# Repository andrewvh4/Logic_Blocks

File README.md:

# Logic_Blocks
Modular, schematic-friendly logic blocks perfect for elementary experimentation with Digital Logic

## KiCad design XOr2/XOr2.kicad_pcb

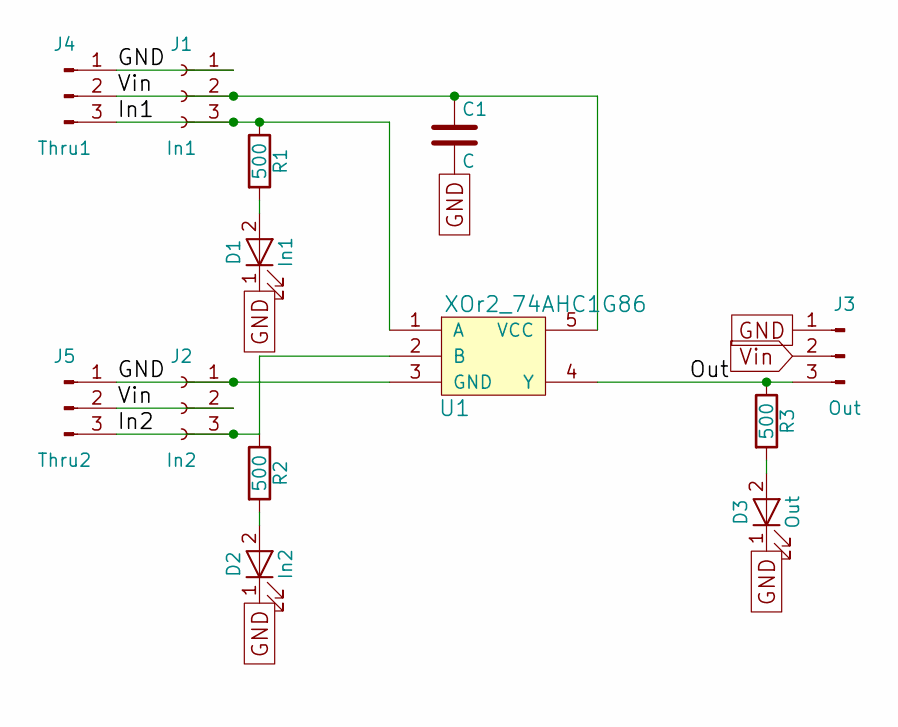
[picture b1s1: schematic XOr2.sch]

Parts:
C1: C; C_0603_HandSoldering
D1: In1; LED_0603_HandSoldering
D2: In2; LED_0603_HandSoldering
D3: Out; LED_0603_HandSoldering
J1: In1; Socket_Strip_Angled_1x03_Pitch2.54mm
J2: In2; Socket_Strip_Angled_1x03_Pitch2.54mm
J3: Out; Pin_Header_Angled_1x03_Pitch2.54mm
J4: Thru1; Pin_Header_Angled_1x03_Pitch2.54mm
J5: Thru2; Pin_Header_Angled_1x03_Pitch2.54mm
R1, R2, R3: 500; R_0603_HandSoldering
U1: XOr2_74AHC1G86; SC_70_1.25mm

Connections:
/In1: J1.3, J4.3, R1.1, U1.1 (A)
/In2: J2.3, J5.3, R2.1, U1.2 (B)
/Out: J3.3, R3.1, U1.4 (Y)
GND: C1.2, D1.1 (K), D2.1 (K), D3.1 (K), J1.1, J2.1, J3.1, J4.1, J5.1, U1.3 (GND)
unnamed: D1.2 (A), R1.2
unnamed: D2.2 (A), R2.2
unnamed: D3.2 (A), R3.2
Vin: C1.1, J1.2, J2.2, J3.2, J4.2, J5.2, U1.5 (VCC)

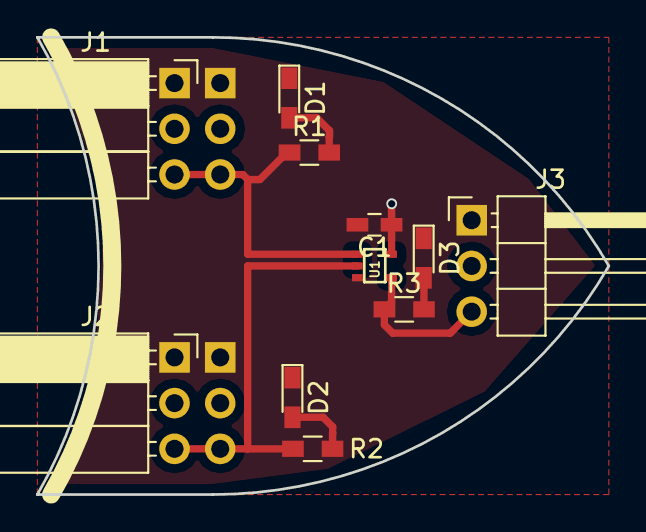
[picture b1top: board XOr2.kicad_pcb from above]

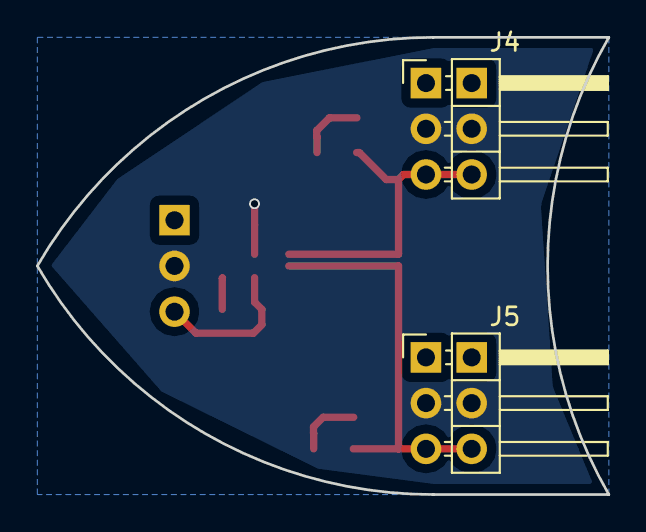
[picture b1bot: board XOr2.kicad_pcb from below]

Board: 2 copper layers, 31.7 x 25.4 mm, 13 parts (2 on the bottom side), 8 nets.

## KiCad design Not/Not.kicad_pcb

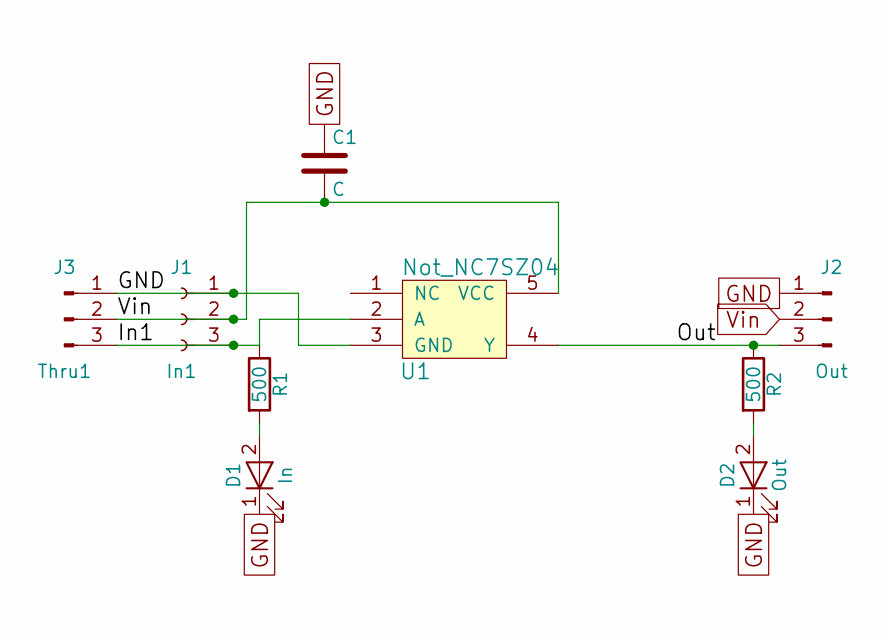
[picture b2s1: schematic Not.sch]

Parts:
C1: C; C_0603_HandSoldering
D1: In; LED_0603_HandSoldering
D2: Out; LED_0603_HandSoldering
J1: In1; Socket_Strip_Angled_1x03_Pitch2.54mm
J2: Out; Pin_Header_Angled_1x03_Pitch2.54mm
J3: Thru1; Pin_Header_Angled_1x03_Pitch2.54mm
R1, R2: 500; R_0603_HandSoldering
U1: Not_NC7SZ04; SC_70_1.25mm

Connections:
/In1: J1.3, J3.3, R1.1, U1.2 (A)
/Out: J2.3, R2.1, U1.4 (Y)
GND: C1.1, D1.1 (K), D2.1 (K), J1.1, J2.1, J3.1, U1.3 (GND)
unnamed: D1.2 (A), R1.2
unnamed: D2.2 (A), R2.2
Vin: C1.2, J1.2, J2.2, J3.2, U1.5 (VCC)

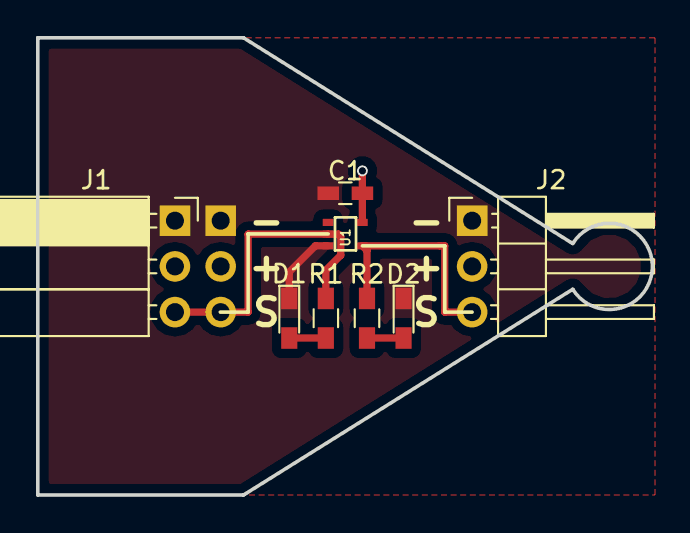
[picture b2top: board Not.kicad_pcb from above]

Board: 2 copper layers, 34.1 x 25.4 mm, 9 parts (1 on the bottom side), 6 nets.

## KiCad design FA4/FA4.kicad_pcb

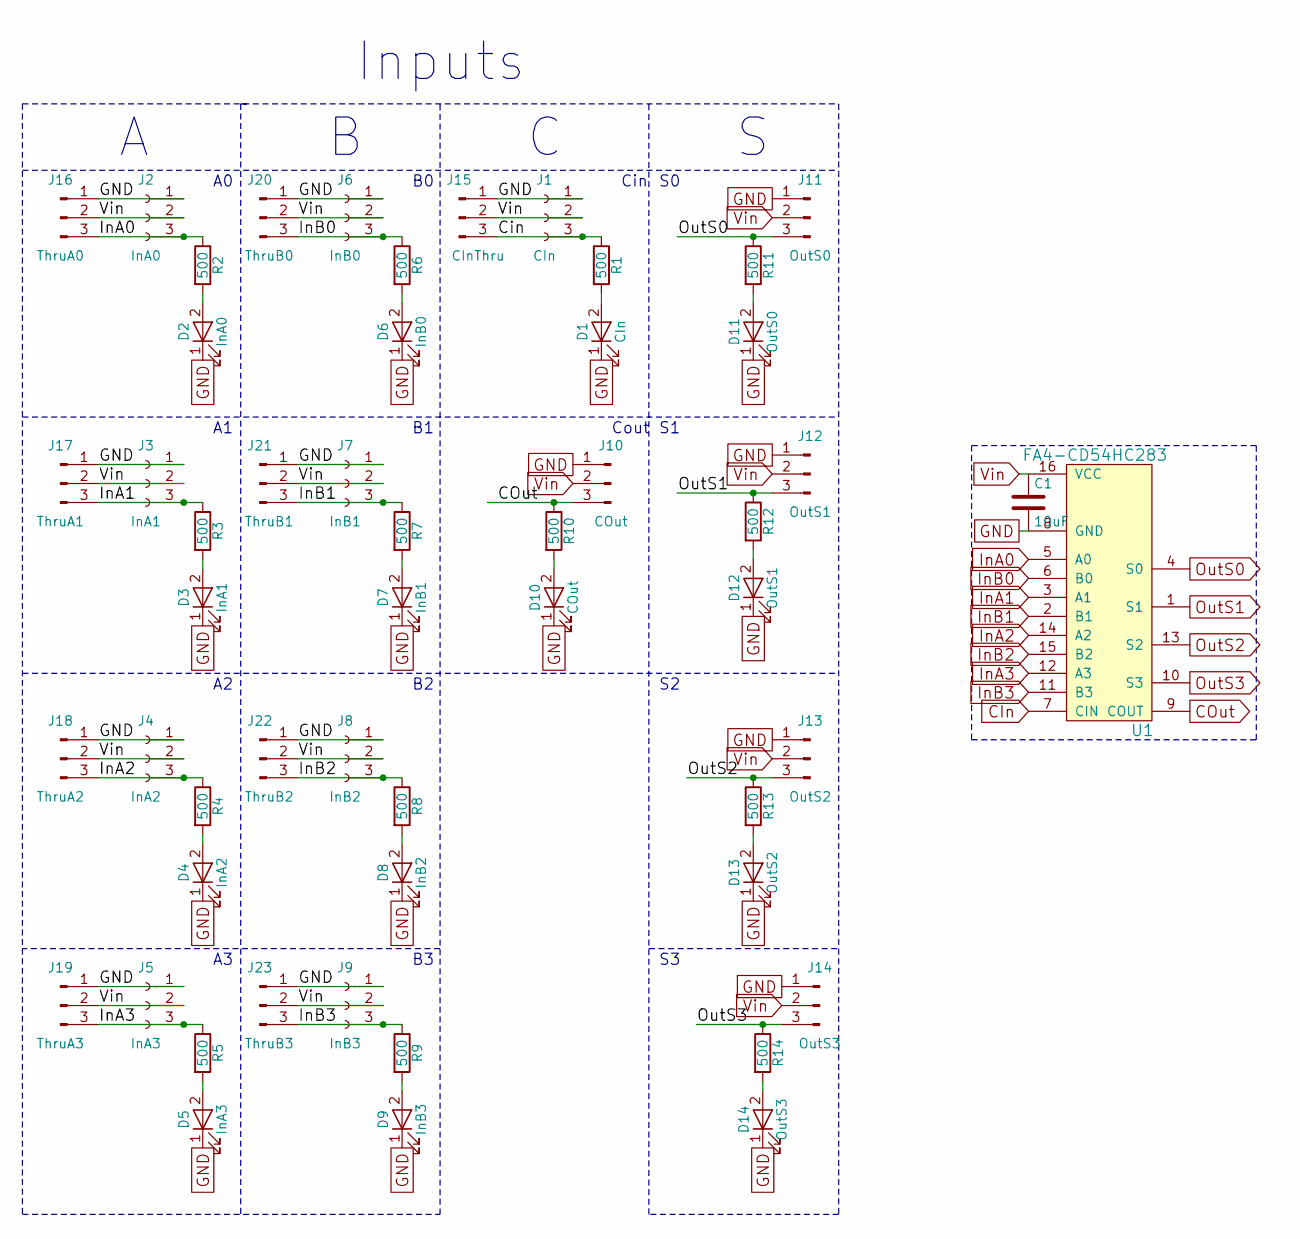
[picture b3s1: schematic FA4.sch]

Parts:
C1: 10uF; C_0603_HandSoldering
D1: CIn; LED_0603_HandSoldering
D2: InA0; LED_0603_HandSoldering
D3: InA1; LED_0603_HandSoldering
D4: InA2; LED_0603_HandSoldering
D5: InA3; LED_0603_HandSoldering
D6: InB0; LED_0603_HandSoldering
D7: InB1; LED_0603_HandSoldering
D8: InB2; LED_0603_HandSoldering
D9: InB3; LED_0603_HandSoldering
D10: COut; LED_0603_HandSoldering
D11: OutS0; LED_0603_HandSoldering
D12: OutS1; LED_0603_HandSoldering
D13: OutS2; LED_0603_HandSoldering
D14: OutS3; LED_0603_HandSoldering
J1: CIn; Socket_Strip_Angled_1x03_Pitch2.54mm
J2: InA0; Socket_Strip_Angled_1x03_Pitch2.54mm
J3: InA1; Socket_Strip_Angled_1x03_Pitch2.54mm
J4: InA2; Socket_Strip_Angled_1x03_Pitch2.54mm
J5: InA3; Socket_Strip_Angled_1x03_Pitch2.54mm
J6: InB0; Socket_Strip_Angled_1x03_Pitch2.54mm
J7: InB1; Socket_Strip_Angled_1x03_Pitch2.54mm
J8: InB2; Socket_Strip_Angled_1x03_Pitch2.54mm
J9: InB3; Socket_Strip_Angled_1x03_Pitch2.54mm
J10: COut; Pin_Header_Angled_1x03_Pitch2.54mm
J11: OutS0; Pin_Header_Angled_1x03_Pitch2.54mm
J12: OutS1; Pin_Header_Angled_1x03_Pitch2.54mm
J13: OutS2; Pin_Header_Angled_1x03_Pitch2.54mm
J14: OutS3; Pin_Header_Angled_1x03_Pitch2.54mm
J15: CInThru; Pin_Header_Angled_1x03_Pitch2.54mm
J16: ThruA0; Pin_Header_Angled_1x03_Pitch2.54mm
J17: ThruA1; Pin_Header_Angled_1x03_Pitch2.54mm
J18: ThruA2; Pin_Header_Angled_1x03_Pitch2.54mm
J19: ThruA3; Pin_Header_Angled_1x03_Pitch2.54mm
J20: ThruB0; Pin_Header_Angled_1x03_Pitch2.54mm
J21: ThruB1; Pin_Header_Angled_1x03_Pitch2.54mm
J22: ThruB2; Pin_Header_Angled_1x03_Pitch2.54mm
J23: ThruB3; Pin_Header_Angled_1x03_Pitch2.54mm
R1, R2, R3, R4, R5, R6, R7, R8, R9, R10, R11, R12, R13, R14: 500; R_0603_HandSoldering
U1: FA4-CD54HC283; SOIC-16W_5.3x10.2mm_Pitch1.27mm

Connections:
CIn: J1.3, J15.3, R1.1, U1.7 (CIN)
COut: J10.3, R10.1, U1.9 (COUT)
GND: C1.2, D1.1 (K), D2.1 (K), D3.1 (K), D4.1 (K), D5.1 (K), D6.1 (K), D7.1 (K), D8.1 (K), D9.1 (K), D10.1 (K), D11.1 (K), D12.1 (K), D13.1 (K), D14.1 (K), J1.1, J2.1, J3.1, J4.1, J5.1, J6.1, J7.1, J8.1, J9.1, J10.1, J11.1, J12.1, J13.1, J14.1, J15.1, J16.1, J17.1, J18.1, J19.1, J20.1, J21.1, J22.1, J23.1, U1.8 (GND)
InA0: J2.3, J16.3, R2.1, U1.5 (A0)
InA1: J3.3, J17.3, R3.1, U1.3 (A1)
InA2: J4.3, J18.3, R4.1, U1.14 (A2)
InA3: J5.3, J19.3, R5.1, U1.12 (A3)
InB0: J6.3, J20.3, R6.1, U1.6 (B0)
InB1: J7.3, J21.3, R7.1, U1.2 (B1)
InB2: J8.3, J22.3, R8.1, U1.15 (B2)
InB3: J9.3, J23.3, R9.1, U1.11 (B3)
unnamed: D1.2 (A), R1.2
unnamed: D2.2 (A), R2.2
unnamed: D3.2 (A), R3.2
unnamed: D4.2 (A), R4.2
unnamed: D5.2 (A), R5.2
unnamed: D6.2 (A), R6.2
unnamed: D7.2 (A), R7.2
unnamed: D8.2 (A), R8.2
unnamed: D9.2 (A), R9.2
unnamed: D10.2 (A), R10.2
unnamed: D11.2 (A), R11.2
unnamed: D12.2 (A), R12.2
unnamed: D13.2 (A), R13.2
unnamed: D14.2 (A), R14.2
OutS0: J11.3, R11.1, U1.4 (S0)
OutS1: J12.3, R12.1, U1.1 (S1)
OutS2: J13.3, R13.1, U1.13 (S2)
OutS3: J14.3, R14.1, U1.10 (S3)
Vin: C1.1, J1.2, J2.2, J3.2, J4.2, J5.2, J6.2, J7.2, J8.2, J9.2, J10.2, J11.2, J12.2, J13.2, J14.2, J15.2, J16.2, J17.2, J18.2, J19.2, J20.2, J21.2, J22.2, J23.2, U1.16 (VCC)

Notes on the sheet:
Inputs
Cin
Cout

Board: 2 copper layers, 53 parts (9 on the bottom side), 30 nets, no tracks yet.

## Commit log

2018-07-23 Created PCBs for certain blocks
2018-08-23 Made XOR Board and modified FA
2018-08-29 Added ToDo
